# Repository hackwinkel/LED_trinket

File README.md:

# trinket

The "trinket" is an electronic gimmick that reacts to the presence of other "trinket"s in the area, and contains a small flashlight.

It was conceived as a demonstration project and target for workshops.

## Folders

* 3D - contains 3D design files (SCAD) for the housing + a soldering aid

* Hardware - contains the schematic and PCB design files

* Workshop - Assembly instructions to go with the trinket soldering workshop

* Software - Firmware for the trinket

## Mixed soldering techniques workshop

The workshop around this badge teaches mixed Surface Mounted Device (SMD) soldering techniques. One side of the Printed circuit board is assembled using a stencil. solder paste and a hotplate for reflowing, the other side is manually populated. In addition there are a few Through-Hole components

## Low voltage or "flat battery" power supply

This trinket contains a boost converter to boost the (nominally 1.5V alkaline battery supply to 5V. This boost converter will start working at battery voltages above ~ 0.9V, but will also keep working until the battery voltage drops below ~ 0.7 V. This is well below the voltages at which alkaline batteries are normally considered empty.

WARNING: empty batteries can leak. Remove empty batteries. This is especially important for this circuit as it was designed to drain batteries as far as it can.

## Infrared communication
This trinket uses IR transmitters and receivers for inter-trinket communications. It uses the well known KISS protocol and should be compatible with other devices using this protocol.

## Flashlight mode
after a button press, 4 white leds light up.

## Blinking lights
When the trinket does not detect a fellow trinket in the neighborhood, it will slowly flash a white light. When another trinket is detected, it displays a pattern of colours.

## ultra low cost microcontrollers
The trinket contains a PADAUK PFS154-S16 microcontroller. The software/hardware *may* also work with a PMS150C-S16 and pin compatible controllers from other manufacturers (e.g. Nyquest tech), but this is untested.

## Programming prerequisites & instructions

You will need a PADAUK programmer to program the device. PADAUK microcontrollers use a proprietary programming algorithm.

Hardware and software for an open source programmer can be found here: https://github.com/free-pdk/easy-pdk-programmer-hardware and https://github.com/free-pdk/easy-pdk-programmer-software.

Follow the instructions provided on these pages.

To compile the software for the label you need:

1. Small Device C Compiler (SDCC) (https://sdcc.sourceforge.net/) version >=4

2. pdk-includes (https://github.com/free-pdk/pdk-includes)

3. easy-pdk-includes (https://github.com/free-pdk/pdk-includes)

3. This repository

Install SDCC as per instructions for your system

Make a containing directory to hold both this repository and the free-pdk  pdk-includes and easy-pdk-includes repositories and:

cd <your_dir>

git clone https://github.com/free-pdk/pdk-includes

git clone https://github.com/free-pdk/easy-pdk-includes

git clone https://github.com/hackwinkel/tag-software

cd tag-software

cd standard

make

make burn

This last command requires easypdkprog to be found in your $PATH. You can also run this command manually

Other make targets are: sizes (displays the sizes of various memory segments in the binary), clean and all (the default).

## alternative firmware

If you want to do something special with your trinket, please do so in an intelligent way, in an IR transmitting envelope that will NOT annoyingly interfere with other badges in your neighborhood:

1. Transmit IR codes once per minute at most

2. Transmit IR codes for one second at most

3. While not transmitting, listen for incoming IR signals, and act accordingly

Note: The PCB design does NOT support in-circuit reprogramming.

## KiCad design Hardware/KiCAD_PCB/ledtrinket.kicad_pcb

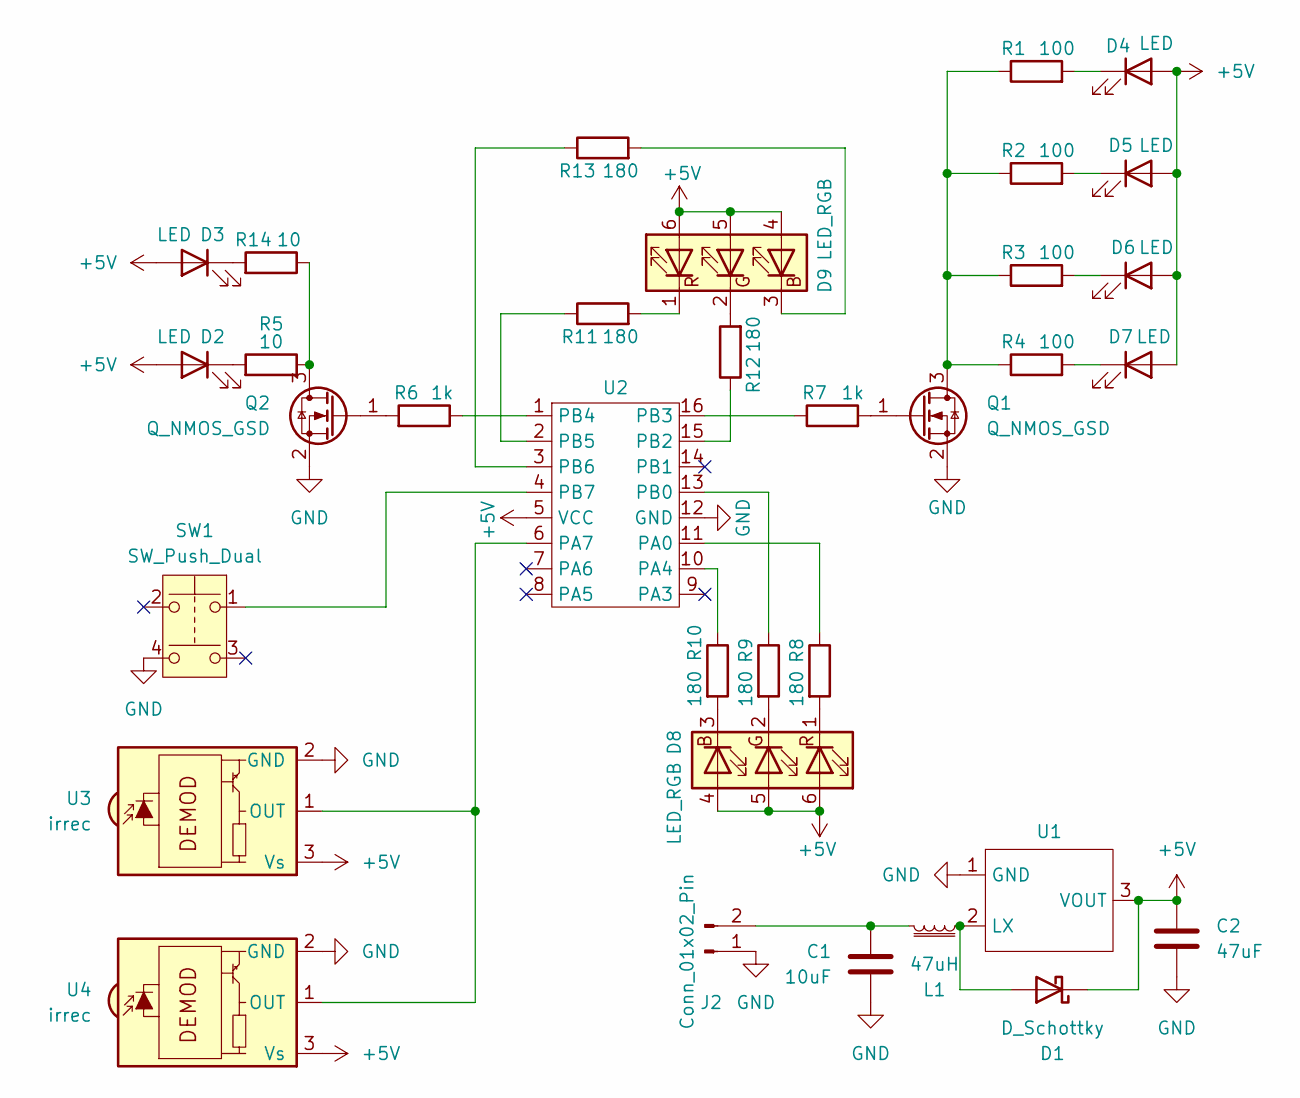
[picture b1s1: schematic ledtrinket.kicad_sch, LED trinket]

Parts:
C1: 10uF; C_0805
C2: 47uF; C_1206
D1: D_Schottky; D_SOD-123
D2, D3: LED; D_2835
D4, D5, D6, D7: LED; led_lamp_th
D8, D9: LED_RGB
J2: Conn_01x02_Pin; powpins
L1: 47uH; L
Q1, Q2: Q_NMOS_GSD; SOT-23
R1, R2, R3, R4: 100; R_0805
R5, R14: 10; R_1206
R6, R7: 1k; R_0805
R8, R9, R10, R11, R12, R13: 180; R_0805
SW1: SW_Push_Dual; button
U1: SOT-23
U2: SOP-16
U3, U4: irrec

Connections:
+5V: C2.1, D1.1 (K), D2.2 (A), D3.2 (A), D4.2 (A), D5.2 (A), D6.2 (A), D7.2 (A), D8.4 (BA), D8.5 (GA), D8.6 (RA), D9.4 (BA), D9.5 (GA), D9.6 (RA), U1.3 (VOUT), U2.5 (VCC), U3.3 (Vs), U4.3 (Vs)
GND: C1.2, C2.2, J2.1, Q1.2 (S), Q2.2 (S), SW1.4, U1.1 (GND), U2.12 (GND), U3.2 (GND), U4.2 (GND)
unnamed: D1.2 (A), L1.1, U1.2 (LX)
unnamed: D2.1 (K), R5.2
unnamed: D3.1 (K), R14.2
unnamed: D4.1 (K), R1.2
unnamed: D5.1 (K), R2.2
unnamed: D6.1 (K), R3.2
unnamed: D7.1 (K), R4.2
unnamed: D8.3 (BK), R10.2
unnamed: D8.2 (GK), R9.2
unnamed: D8.1 (RK), R8.2
unnamed: D9.3 (BK), R13.2
unnamed: D9.2 (GK), R12.2
unnamed: D9.1 (RK), R11.2
unnamed: C1.1, J2.2, L1.2
unnamed: Q1.3 (D), R1.1, R2.1, R3.1, R4.1
unnamed: Q1.1 (G), R7.2
unnamed: Q2.3 (D), R5.1, R14.1
unnamed: Q2.1 (G), R6.2
unnamed: R8.1, U2.11 (PA0)
unnamed: R10.1, U2.10 (PA4)
unnamed: U2.6 (PA7), U3.1 (OUT), U4.1 (OUT)
unnamed: R9.1, U2.13 (PB0)
unnamed: R12.1, U2.15 (PB2)
unnamed: R7.1, U2.16 (PB3)
unnamed: R6.1, U2.1 (PB4)
unnamed: R11.1, U2.2 (PB5)
unnamed: R13.1, U2.3 (PB6)
unnamed: SW1.1, U2.4 (PB7)

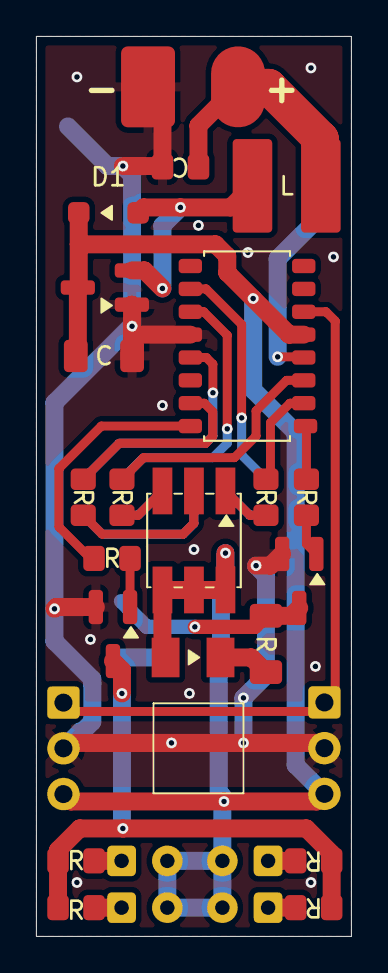
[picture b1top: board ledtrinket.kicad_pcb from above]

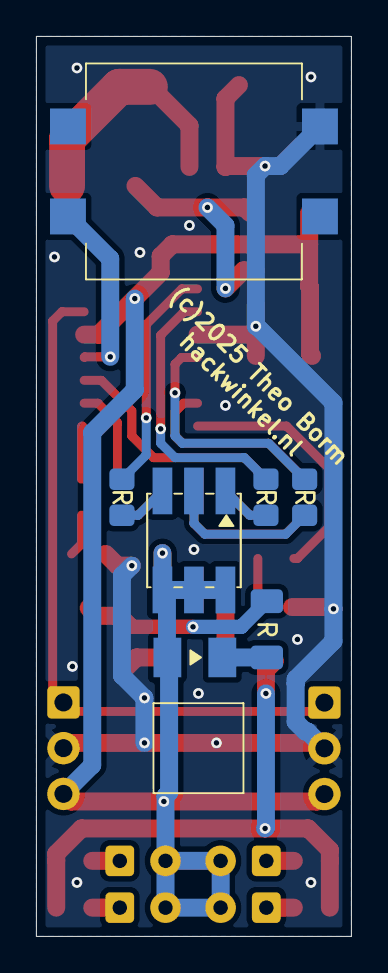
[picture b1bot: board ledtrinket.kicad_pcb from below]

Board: 2 copper layers, 17.5 x 50.0 mm, 34 parts (8 on the bottom side), 30 nets.

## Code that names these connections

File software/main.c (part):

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* PFS154 pin assignment
* 
* pin	dir	func	active
* PA0	out	RGB1_R	low
* PA3	out	DEBUGIR	low
* PA4	out	RGB1_B	low
* PA5	n.c.	n.a.	n.a.
* PA6	n.c.	n.a.	n.a.
* PA7	in,p.u.	IR_IN	low
* PB0	out	RGB1_G	low	
* PB1	n.c.	n.a.	n.a.
* PB2	out	RGB2_G	low
* PB3	out	LIGHT	high
* PB4	out	IR_OUT	high
* PB5	out	RGB2_R	low
* PB6	out	RGB2_B	low
* PB7	in,p.u.	BUTTON	low
*/
/*
* PA3, PA5, PA6 and PB1 are used as debug status outputs
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		switch (fstate) {
			case 0:
				if (buttonstate) {
					// switch flashlight on (by setting PB3 high), and all other leds off
					PA |= 0b00010001;	
					PB |= 0b01101101;	

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			case 2:
				if (buttonstate==1) {
					fstate=3;
					// switch off the flashlight (by setting PB3 low)
					PB &=0x77;
					ftimeout=500;
				} else if (ftimeout==0) {
					// switch off the flashlight (by setting PB3 low)
					PB &=0x77;
					fstate=0;
				}
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					fstate=0;
				} else if (ftimeout==0) {
					fstate=4;
					// switch flashlight on (by setting PB3 high), and all other leds off
					PA |= 0b00010001;	
					PB |= 0b01101101;	
					ftimeout=500;
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				break;
			case 4: if (buttonstate==0) {
					fstate=0;
					// switch off the flashlight (by setting PB3 low)
					PB &=0x77;
				} else if (ftimeout==0) {
					fstate=3;
					// switch off the flashlight (by setting PB3 low)
					PB &=0x77;
					ftimeout=500;
				}
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				if (buttonstate==1) {
					PA |= 0x40; // debug flashlight signal off
					fstate=3;
					// switch off the flashlight (by setting PB3 low)
					PB &=0x77;
					ftimeout=500;
				} else if (ftimeout==0) {
					PA |= 0x40; // debug flashlight signal off
					fstate=7;
					// switch off the flashlight (by setting PB3 low)
					PB &=0x77;
					ftimeout=100;
				}
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			case 7:
				if (ftimeout==0) {
					fstate=8;
					// switch flashlight on (by setting PB3 high), and all other leds off
					PA |= 0b00010001;	
					PB |= 0b01101101;	
					ftimeout=2000;
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					fstate=5;
				} else if (ftimeout==0) {
					fstate=0;
					// switch off the flashlight (by setting PB3 low)
					PB &=0x77;
				}
				break;	
		}
		
		
		/* we use timer 2 to generate a  38kHz sync pulse on PB4. These settings are necessary:
		* IHRC 16MHz, 16000000/422=37.914 KHz
		* TM2C [7:4]=0010 (select IHRC); [3:2]=11 (output on PB4); [1] = 0 (period mode); [0] = 0 (do not invert);
		* TM2S [7] = 0 (8 bit resolution); [6:5]=00 (prescaler 1); [4:0]=00000 (scaler 1);
		* TM2B [7:0] -> 211
		*/
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*/
void main(void) {
	// Initialize hardware:
	//PA0-6 are ACTIVE LOW, so set them HIGH before making them outputs
	//PB0-2 & PB5-6 are ACTIVE LOW, so set them HIGH before making them outputs
	PA=0x7f;	
	PB=0x67;	
	
  	//ENABLE pull-ups on PA5, PA7, PB7, DISABLE on all other pins
	PAPH = 0xA0; // 10100000
	PBPH = 0x80; // 10000000
	
	// PA0-6 and PB0-6 are OUTPUTS
	PAC=0x7f;
	PBC=0x7f;
  	
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
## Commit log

2025-07-17 Update README.md
    mainly typos

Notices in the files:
software/main.c:
(c) 2025 by Theo Borm
see LICENSE file in this repository
Hardware/KiCAD_PCB/ledtrinket.kicad_pcb:
(c)2025 Theo Borm
